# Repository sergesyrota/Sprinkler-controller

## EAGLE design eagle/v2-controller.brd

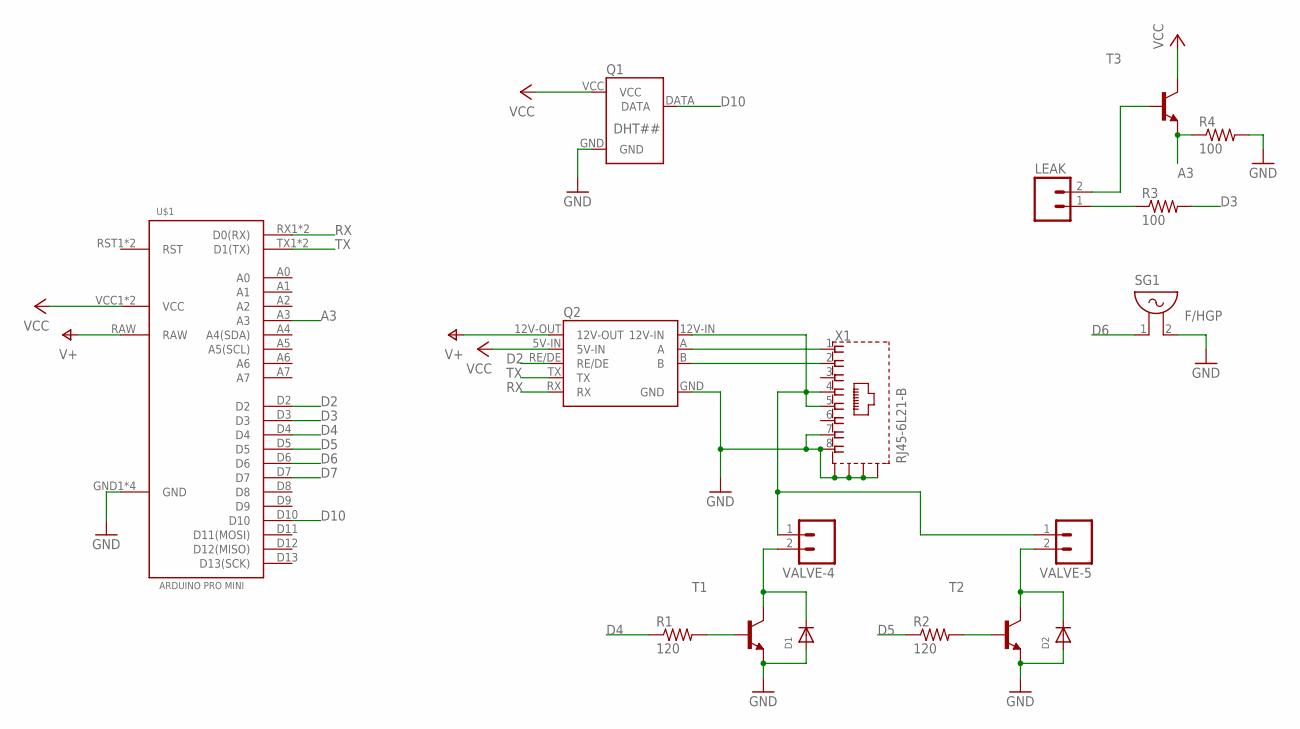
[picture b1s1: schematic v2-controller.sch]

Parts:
D1, D2: DIODESMA; SMADIODE
LEAK: M02; 02P
Q1: DHT##; CONNECTOR-4-PIN-0.1
Q2: RS485-ADAPTER0.05-CONNECTOR; RS485-ADAPTOR-05
R1, R2: 120; R0603
R3, R4: 100; R0603
SG1: F/HGP
T1, T2, T3: BC808-NPN-SOT23-BEC; SOT23-BEC
U$1: ARDUINO-PRO-MINI
VALVE-4, VALVE-5: M02; 02P
X1: RJ45-6L21-B; RJ45-SHIELD1

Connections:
A3: R4.1, T3.E, U$1.A3
D2: Q2.RE/DE, U$1.D2
D3: R3.2, U$1.D3
D4: R1.1, U$1.D4
D5: R2.1, U$1.D5
D6: SG1.1, U$1.D6
D7: U$1.D7
D10: Q1.DATA, U$1.D10
GND: D1.A, D2.A, Q1.GND, Q2.GND, R4.2, SG1.2, T1.E, T2.E, U$1.GND1 (GND), U$1.GND2 (GND), U$1.GND3 (GND), U$1.GND4 (GND), X1.7, X1.8, X1.S1 (S), X1.S2 (S), X1.S3 (S), X1.S4 (S)
unnamed: LEAK.1, R3.1
unnamed: R1.2, T1.B
unnamed: LEAK.2, T3.B
unnamed: Q2.12V-IN, VALVE-4.1, VALVE-5.1, X1.4, X1.5
unnamed: D2.C, T2.C, VALVE-5.2
unnamed: Q2.B, X1.2
unnamed: Q2.A, X1.1
unnamed: D1.C, T1.C, VALVE-4.2
unnamed: R2.2, T2.B
RX: Q2.RX, U$1.RX1 (D0(RX)), U$1.RX2 (D0(RX))
TX: Q2.TX, U$1.TX1 (D1(TX)), U$1.TX2 (D1(TX))
V+: Q2.12V-OUT, U$1.RAW
VCC: Q1.VCC, Q2.5V-IN, T3.C, U$1.VCC1 (VCC), U$1.VCC2 (VCC)

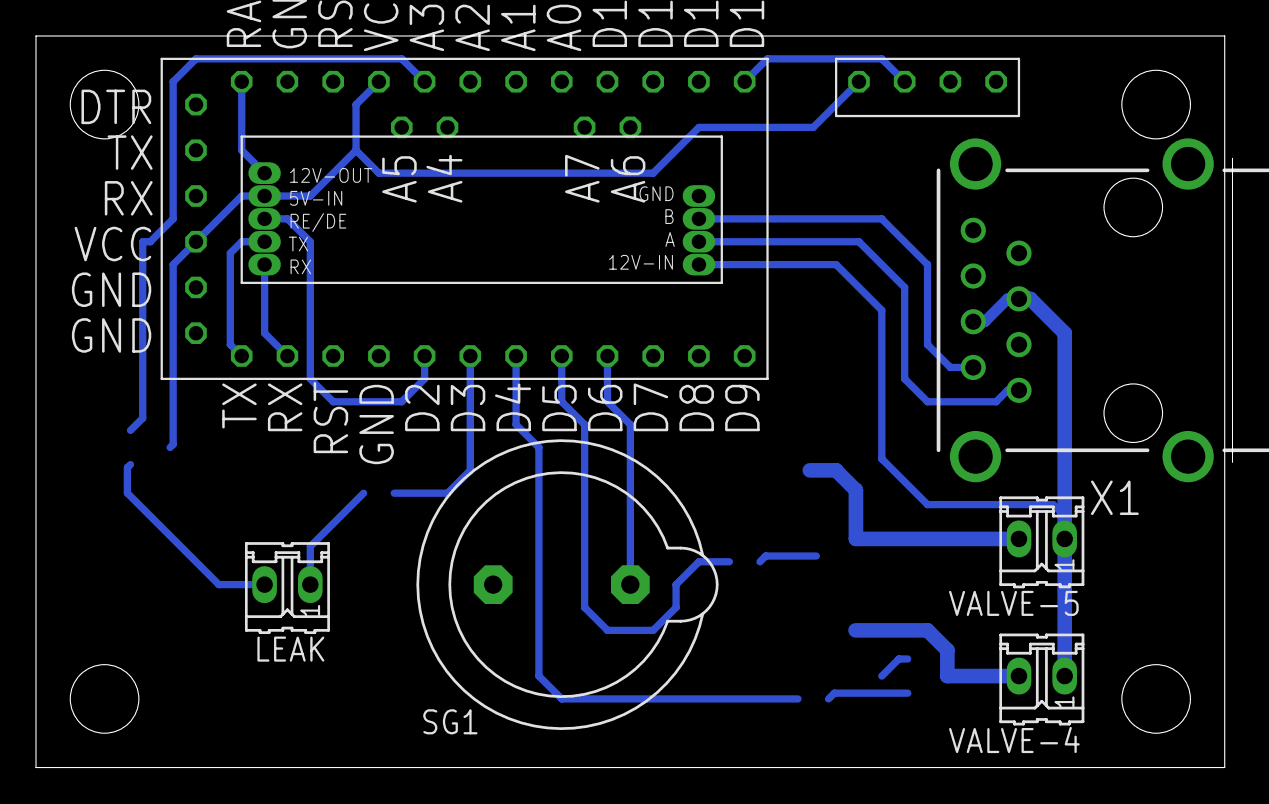
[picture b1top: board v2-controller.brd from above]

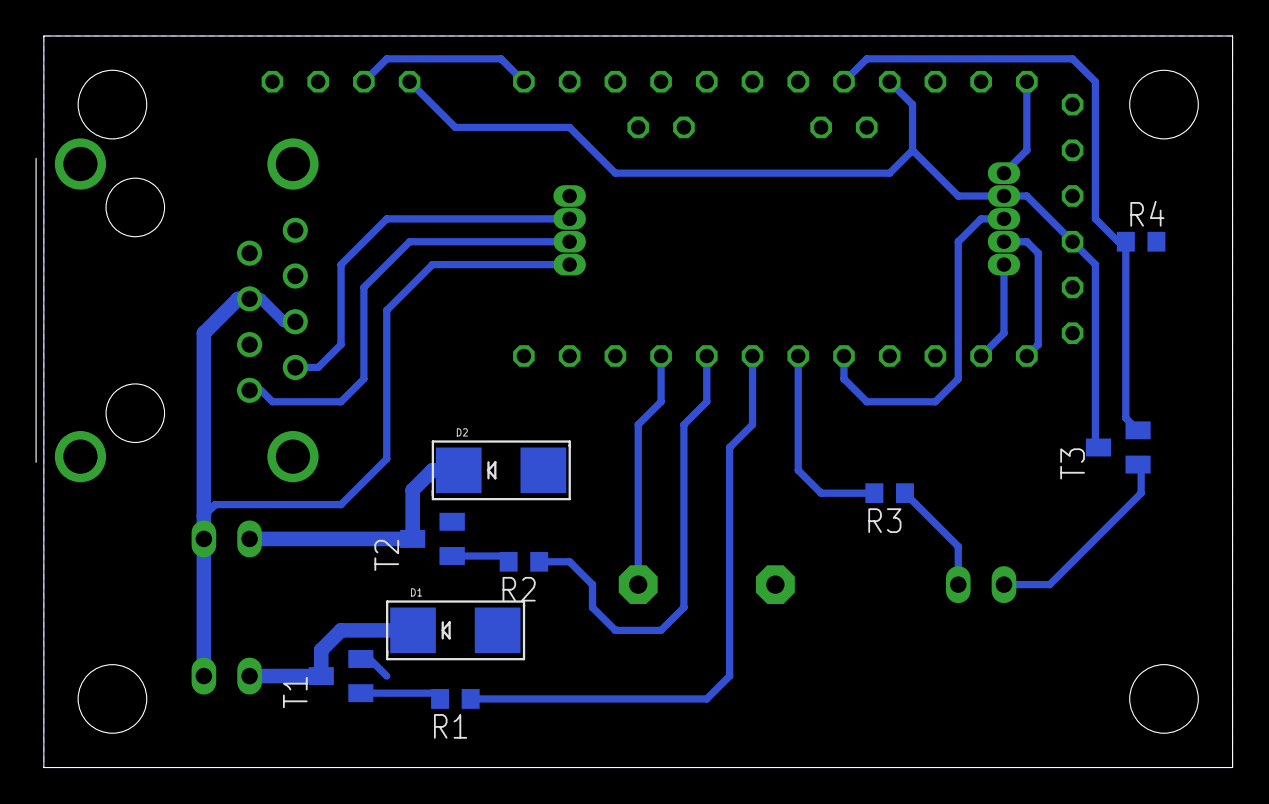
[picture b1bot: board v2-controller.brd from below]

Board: 2 copper layers, 66.5 x 40.6 mm, 17 parts (9 on the bottom side), 21 nets.

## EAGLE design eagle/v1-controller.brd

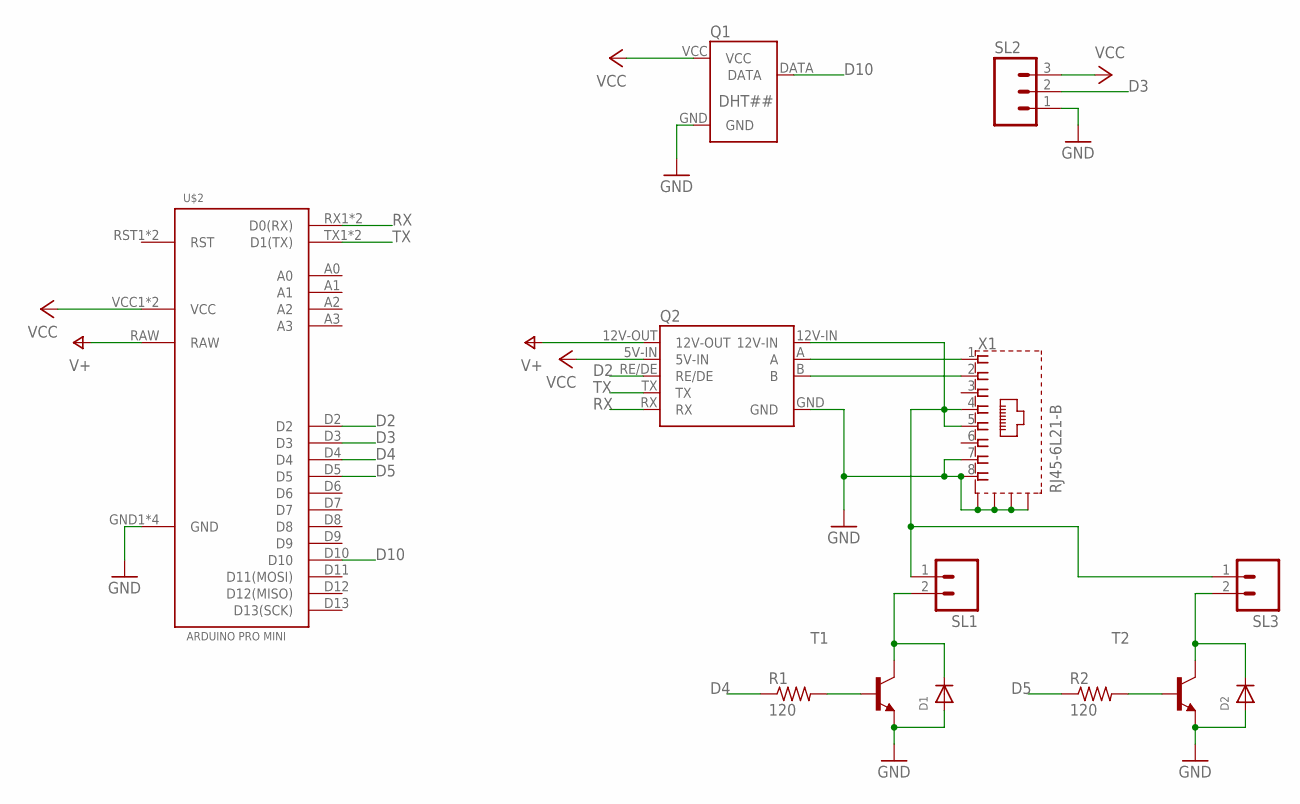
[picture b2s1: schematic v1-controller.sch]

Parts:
D1, D2: DIODESMA; SMADIODE
Q1: DHT##; CONNECTOR-4-PIN-0.1
Q2: RS485-ADAPTER0.05-CONNECTOR; RS485-ADAPTOR-05
R1, R2: 120; R0603
SL1, SL3: M02; 02P
SL2: M03; 03P
T1, T2: BC808-NPN-SOT23-BEC; SOT23-BEC
U$2: ARDUINO-PRO-MINI
X1: RJ45-6L21-B; RJ45-SHIELD1

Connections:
D2: Q2.RE/DE, U$2.D2
D3: SL2.2, U$2.D3
D4: R1.1, U$2.D4
D5: R2.1, U$2.D5
D10: Q1.DATA, U$2.D10
GND: D1.A, D2.A, Q1.GND, Q2.GND, SL2.1, T1.E, T2.E, U$2.GND1 (GND), U$2.GND2 (GND), U$2.GND3 (GND), U$2.GND4 (GND), X1.7, X1.8, X1.S1 (S), X1.S2 (S), X1.S3 (S), X1.S4 (S)
unnamed: R1.2, T1.B
unnamed: Q2.12V-IN, SL1.1, SL3.1, X1.4, X1.5
unnamed: D2.C, SL3.2, T2.C
unnamed: Q2.B, X1.2
unnamed: Q2.A, X1.1
unnamed: D1.C, SL1.2, T1.C
unnamed: R2.2, T2.B
RX: Q2.RX, U$2.RX1 (D0(RX)), U$2.RX2 (D0(RX))
TX: Q2.TX, U$2.TX1 (D1(TX)), U$2.TX2 (D1(TX))
V+: Q2.12V-OUT, U$2.RAW
VCC: Q1.VCC, Q2.5V-IN, SL2.3, U$2.VCC1 (VCC), U$2.VCC2 (VCC)

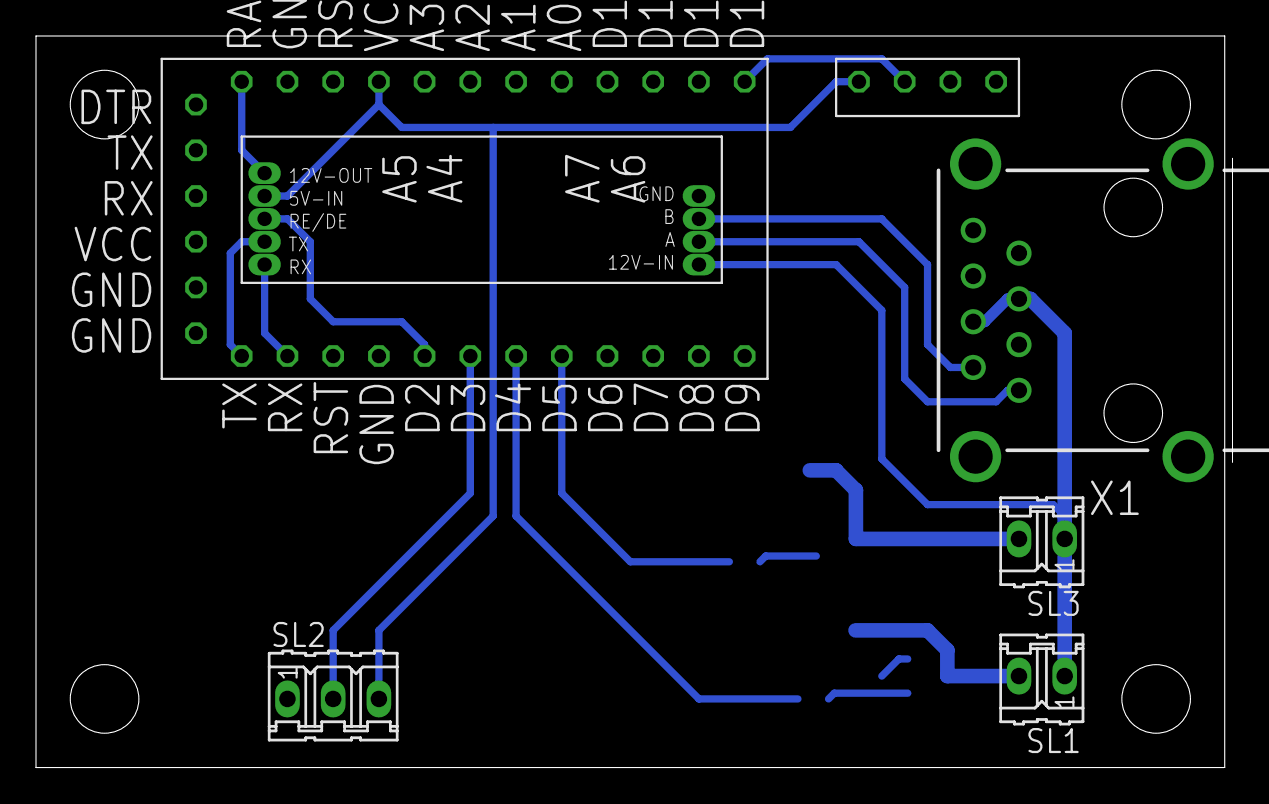
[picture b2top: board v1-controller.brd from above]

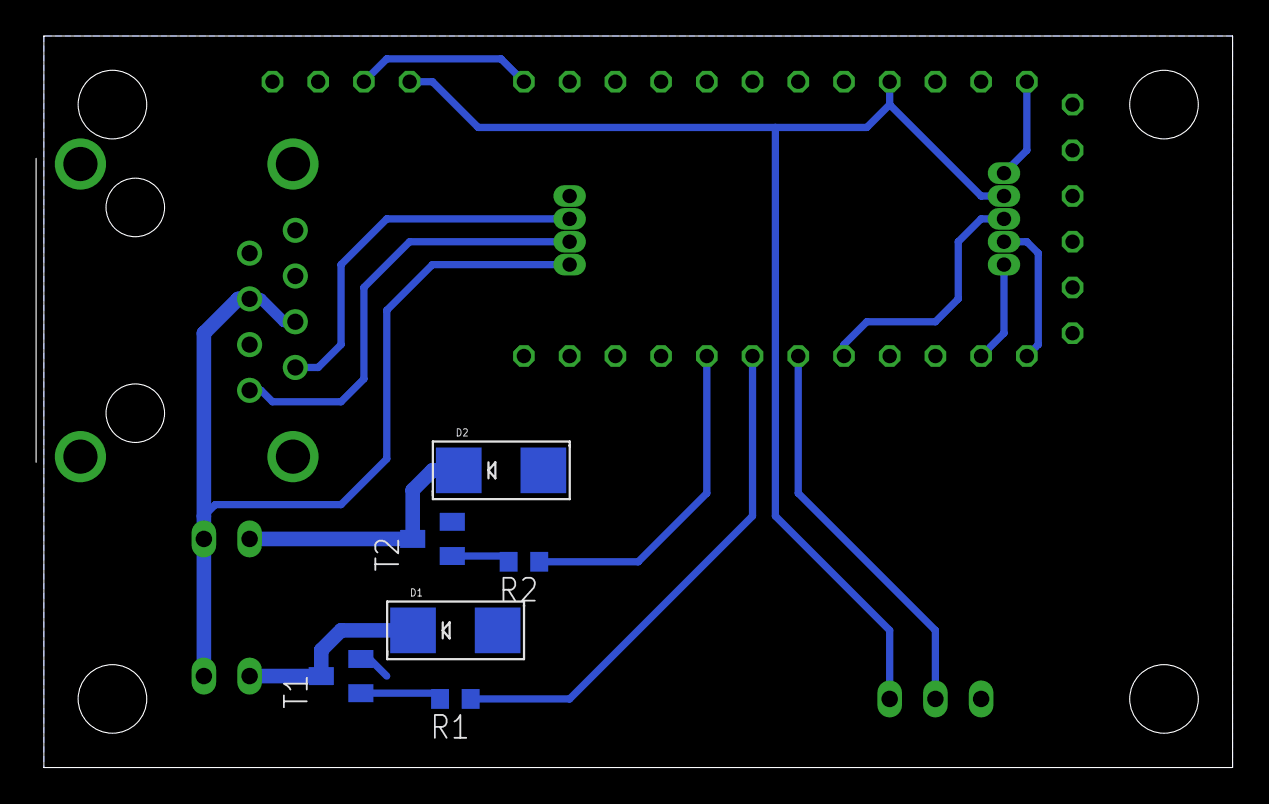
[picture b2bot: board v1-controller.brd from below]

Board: 2 copper layers, 66.5 x 40.6 mm, 13 parts (6 on the bottom side), 17 nets.

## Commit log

2015-07-11 Finished the board, just starting on the code
2015-12-22 Adding Valve constsnts and struct, as well as finishing the sketch.
2015-12-22 Finished v1
2015-12-22 v2 of controller: now has analog leak sensor, and removed motion sensor.
2015-12-23 Moving v2 sprinkler board controls to the same location. Adding a buzzed for alerting when water leak is detected.
2015-12-23 Fixed going over analog pins for one of the traces.
2016-01-03 Adding leak sensor logic
